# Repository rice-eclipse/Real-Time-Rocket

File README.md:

# Neutro Board
Repository stored on the raspberry pi used for Spaceport America Cup 2023 and launch test in Spring 2023. The scripts activates the sensors on Neutro, collects data, and transmit to the ground station NARWAL.

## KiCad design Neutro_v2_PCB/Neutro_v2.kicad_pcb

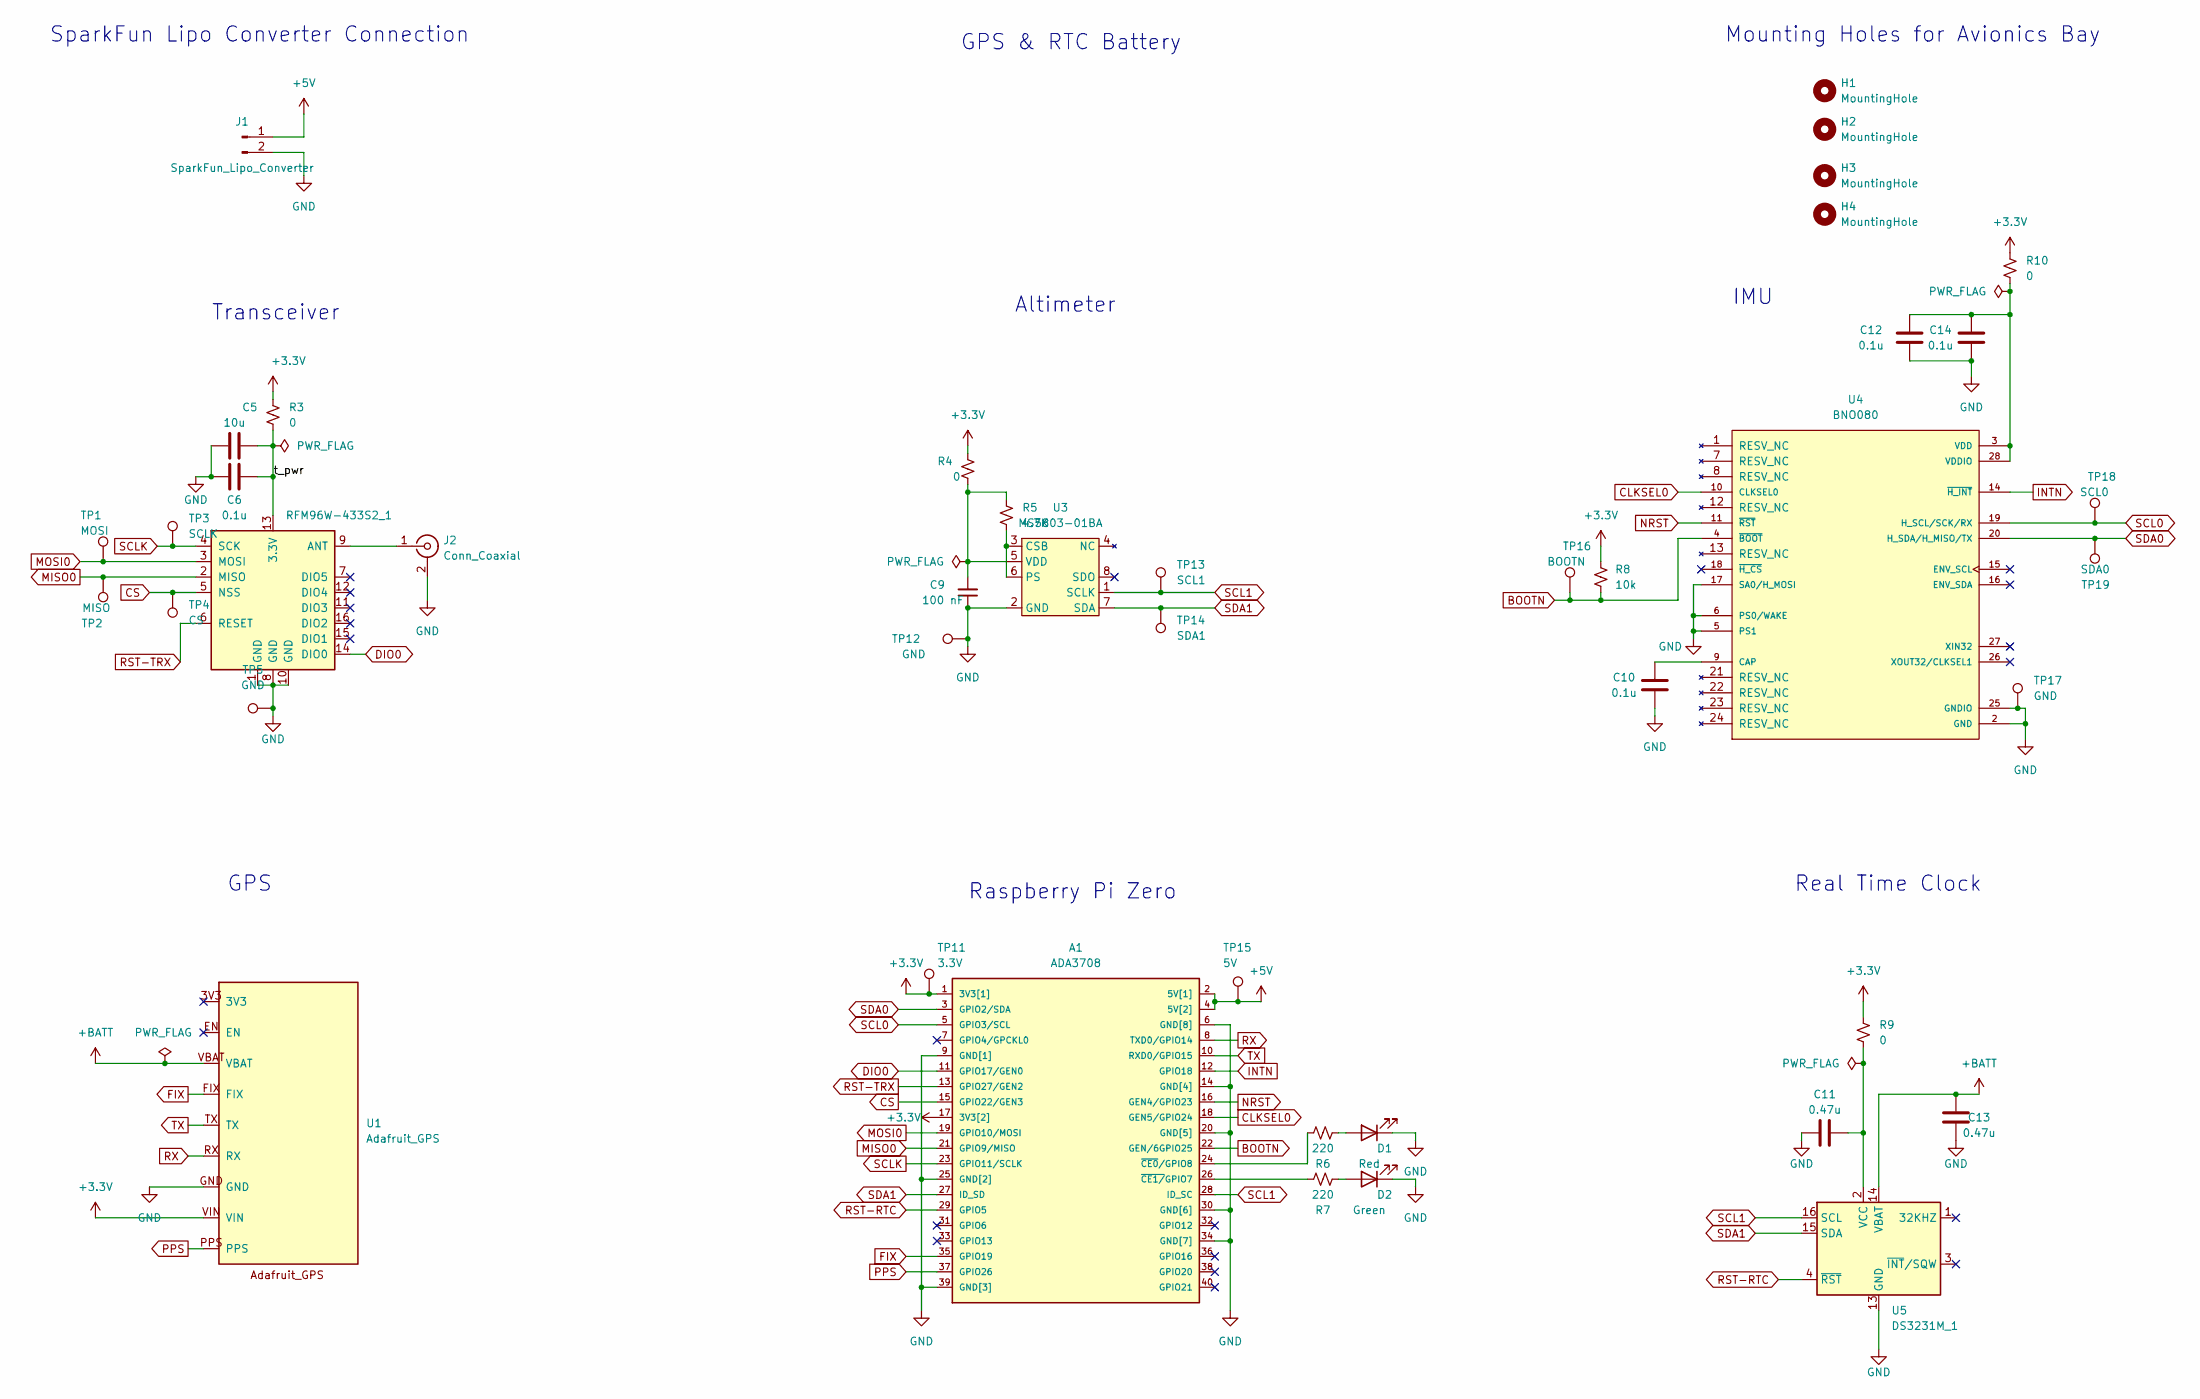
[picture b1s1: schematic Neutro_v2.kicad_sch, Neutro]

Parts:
A1: ADA3708; ADA3708_RPI-ZERO
C5: 10u; C_1206_3216Metric
C6, C10, C12, C14: 0.1u; C_1206_3216Metric
C9: 100 nF; C_1206_3216Metric
C11, C13: 0.47u; C_1206_3216Metric
D1: Red; LED_D3.0mm
D2: Green; LED_D3.0mm
H1, H2, H3, H4: MountingHole; MountingHole_2.5mm
J1: SparkFun_Lipo_Converter; Sparkfun_Lipo_Converter
J2: Conn_Coaxial; SMA_Amphenol_132203-12_Horizontal
R3, R4, R9, R10: 0; R_1206_3216Metric
R5: 4.7K; R_1206_3216Metric
R6, R7: 220; R_1206_3216Metric
R8: 10k; R_1206_3216Metric
TP1: MOSI; TestPoint_THTPad_D1.5mm_Drill0.7mm
TP2: MISO; TestPoint_THTPad_D1.5mm_Drill0.7mm
TP3: SCLK; TestPoint_THTPad_D1.5mm_Drill0.7mm
TP4: CS; TestPoint_THTPad_D1.5mm_Drill0.7mm
TP5, TP12, TP17: GND; TestPoint_THTPad_D1.5mm_Drill0.7mm
TP11: 3.3V; TestPoint_THTPad_D1.5mm_Drill0.7mm
TP13: SCL1; TestPoint_THTPad_D1.5mm_Drill0.7mm
TP14: SDA1; TestPoint_THTPad_D1.5mm_Drill0.7mm
TP15: 5V; TestPoint_THTPad_D1.5mm_Drill0.7mm
TP16: BOOTN; TestPoint_THTPad_D1.5mm_Drill0.7mm
TP18: SCL0; TestPoint_THTPad_D1.5mm_Drill0.7mm
TP19: SDA0; TestPoint_THTPad_D1.5mm_Drill0.7mm
U1: Adafruit_GPS
U2: RFM96W-433S2_1; HOPERF_RFM9XW_SMD
U3: MS5803-01BA; MS5803-01BA_Miniature_Altimeter_Module
U4: BNO080; BNO085; PARTREV 1.6
U5: DS3231M_1; DS3231M

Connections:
+3.3V: A1.1 (3V3[1]), A1.17 (3V3[2]), R3.1, R4.1, R8.1, R9.1, R10.1, TP11.1, U1.VIN
+5V: A1.2 (5V[1]), A1.4 (5V[2]), J1.1, TP15.1
+BATT: C13.1, U1.VBAT, U5.14 (VBAT)
/t_pwr: C5.2, C6.2, R3.2, U2.13 (3.3V)
BOOTN: A1.22 (GEN/6GPIO25), R8.2, TP16.1, U4.4 (~BOOT)
CLKSEL0: A1.18 (GEN5/GPIO24), U4.10 (CLKSEL0)
CS: A1.15 (GPIO22/GEN3), TP4.1, U2.5 (NSS)
DIO0: A1.11 (GPIO17/GEN0), U2.14 (DIO0)
FIX: A1.35 (GPIO19), U1.FIX
GND: A1.6 (GND[8]), A1.9 (GND[1]), A1.14 (GND[4]), A1.20 (GND[5]), A1.25 (GND[2]), A1.30 (GND[6]), A1.34 (GND[7]), A1.39 (GND[3]), C5.1, C6.1, C9.1, C10.1, C11.1, C12.1, C13.2, C14.1, D1.1 (K), D2.1 (K), J1.2, J2.2 (Ext), TP5.1, TP12.1, TP17.1, U1.GND, U2.1 (GND), U2.8 (GND), U2.10 (GND), U3.2 (GND), U4.2 (GND), U4.5 (PS1), U4.6 (PS0/WAKE), U4.17 (SA0/H_MOSI), U4.25 (GNDIO), U5.5 (GND), U5.6 (GND), U5.7 (GND), U5.8 (GND), U5.9 (GND), U5.10 (GND), U5.11 (GND), U5.12 (GND), U5.13 (GND)
INTN: A1.12 (GPIO18), U4.14 (~H_INT)
MISO0: A1.21 (GPIO9/MISO), TP2.1, U2.2 (MISO)
MOSI0: A1.19 (GPIO10/MOSI), TP1.1, U2.3 (MOSI)
NRST: A1.16 (GEN4/GPIO23), U4.11 (~RST)
unnamed: A1.24 (~CE0/GPIO8), R6.1
unnamed: A1.26 (~CE1/GPIO7), R7.1
unnamed: C9.2, R4.2, R5.1, U3.5 (VDD)
unnamed: C10.2, U4.9 (CAP)
unnamed: C11.2, R9.2, U5.2 (VCC)
unnamed: C12.2, C14.2, R10.2, U4.3 (VDD), U4.28 (VDDIO)
unnamed: D1.2 (A), R6.2
unnamed: D2.2 (A), R7.2
unnamed: J2.1 (In), U2.9 (ANT)
unnamed: R5.2, U3.3 (CSB), U3.6 (PS)
PPS: A1.37 (GPIO26), U1.PPS
RST-RTC: A1.29 (GPIO5), U5.4 (~RST)
RST-TRX: A1.13 (GPIO27/GEN2), U2.6 (RESET)
RX: A1.8 (TXD0/GPIO14), U1.RX
SCL0: A1.5 (GPIO3/SCL), TP18.1, U4.19 (H_SCL/SCK/RX)
SCL1: A1.28 (ID_SC), TP13.1, U3.1 (SCLK), U5.16 (SCL)
SCLK: A1.23 (GPIO11/SCLK), TP3.1, U2.4 (SCK)
SDA0: A1.3 (GPIO2/SDA), TP19.1, U4.20 (H_SDA/H_MISO/TX)
SDA1: A1.27 (ID_SD), TP14.1, U3.7 (SDA), U5.15 (SDA)
TX: A1.10 (RXD0/GPIO15), U1.TX

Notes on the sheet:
IMU
Raspberry Pi Zero
GPS & RTC Battery
SparkFun Lipo Converter Connection
GPS
Altimeter
Real Time Clock
Transceiver
Mounting Holes for Avionics Bay

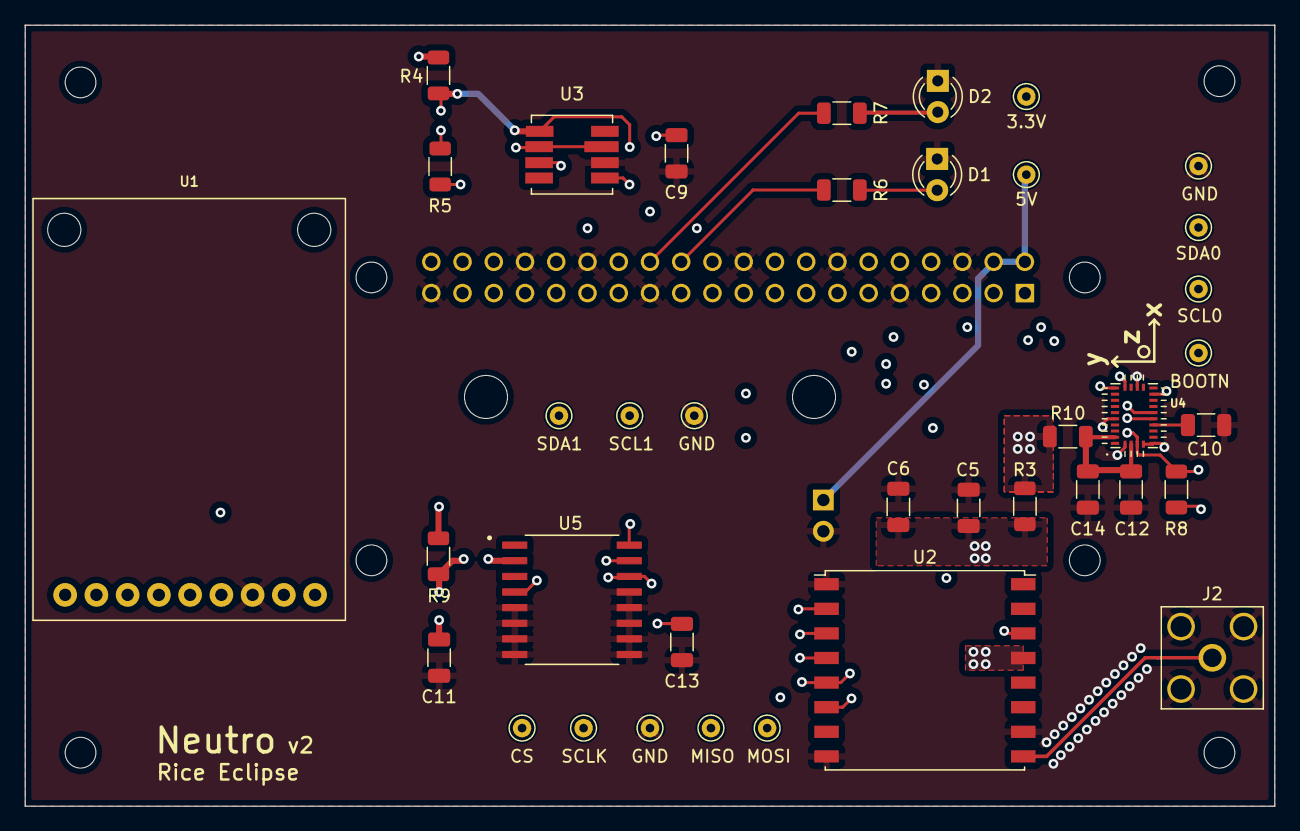
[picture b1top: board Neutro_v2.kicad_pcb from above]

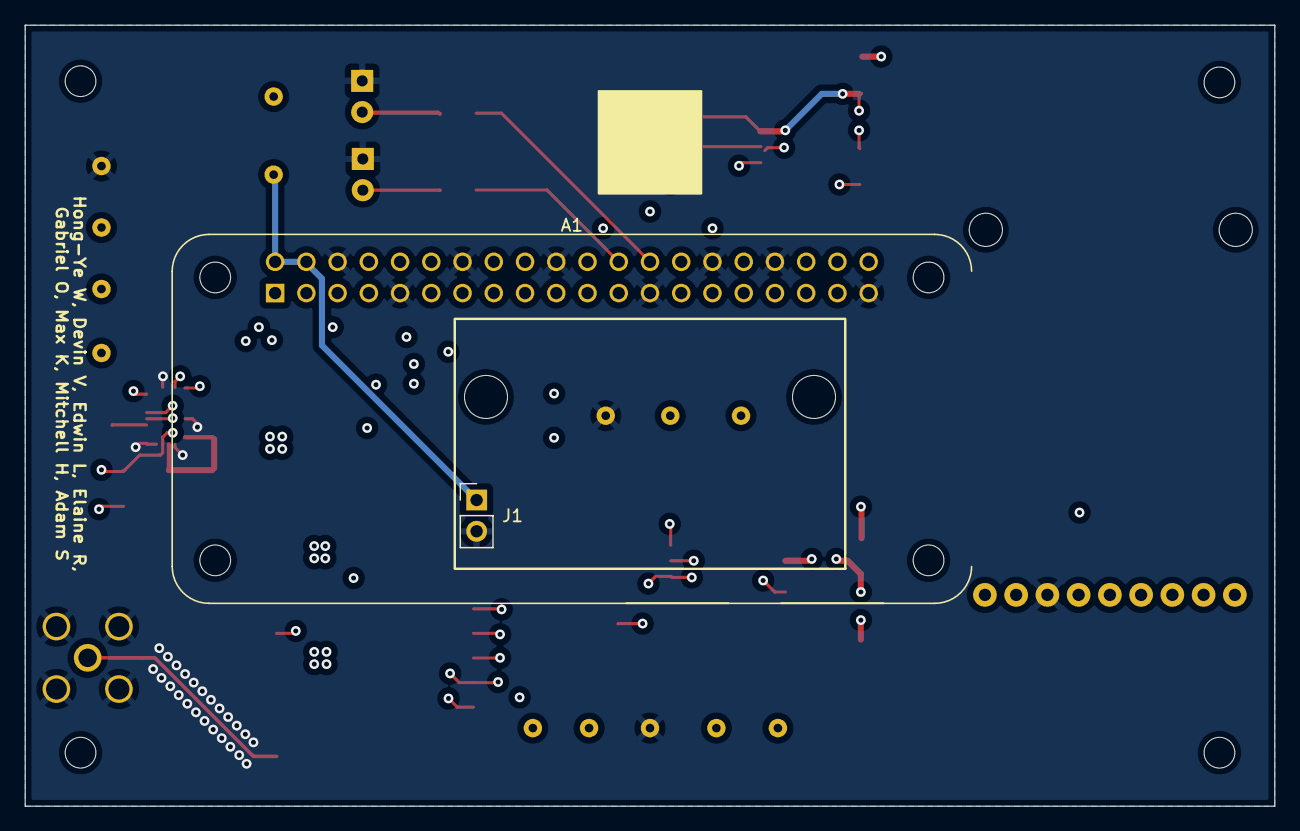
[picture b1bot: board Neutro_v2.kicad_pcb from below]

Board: 4 copper layers, 101.6 x 63.5 mm, 44 parts (2 on the bottom side), 34 nets.

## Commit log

2018-10-26 Initial commit for Real-Time-Rocket
2018-10-26 Initial Commit pt 2
2018-10-26 Rename Reciever_Code.ino to Reciever.ino
2018-10-26 Rename Transmitter_Code.ino to Transmitter.ino
2018-11-08 Added barebones transmission test for certs
    Just transmits incrementing numbers as fast as possible and logs to
    local SD. Receiver prints values to serial but does not log to any
    external source yet. Kept original factory examples in Examples folder.
2018-11-08 Added pressure/altitude/temperature sensor
2018-11-09 Created a local logging script
    Alternative to simply copy-pasting from Arduino serial monitor.
    Requires the Processing language to be installed. Put it on Hammer,
    might come in handy for the certs test.
2018-11-10 Now creates a new logfile on every run
2019-01-25 Changed Altitude function call from AltitudeFt to getAltitude
2019-01-25 Added faster transmitter code
2019-03-01 Changed pin definitions to keep consistent with Transmitter code
2019-08-13 Folder restructuring
2019-08-14 Added libraries and components for RTR
2019-08-16 Add battery holder library file
2019-08-16 Slight verification and modification of library files
2019-08-20 Add main RTR schematic (missing extra Li-Po power circuitry)
2019-08-22 Finalize schematic
2019-08-22 Add power circuitry libraries and update part footprints
2019-08-22 Add reference datasheets
2019-08-22 Update datasheets, small schematic revisions, add test pins
2019-08-24 Lay out components logically on board, miscellaneous library and schematic additions and fixes
2019-08-30 Route Board
2019-08-31 Increase size of and reroute VCC and VCC_5V traces throughout the board
2019-08-31 Update EAGLE version and small miscellaneous documentation/functionality fixes
2019-08-31 Add CAM file for ordering
2019-09-14 Added IMU datasheet
2019-09-21 Add Antenova datasheets
2019-09-21 Add symbol for M20050-1 gps
2019-09-22 initialize imu breakout project (port and imu components made)
2019-09-22 Update file names
2019-09-28 Add m20050-1 device in EAGLE
2019-09-29 added accel code
2019-10-11 Initial Commit for Transmitter code for ProtoV1
2019-10-12 Update libraries and add all sensor support
2019-10-16 Add zero calibration
2019-10-16 Clean up unnecessary files
2019-10-16 Update gitignore
2019-10-16 Add Kevin's Transciever breakout board
2019-10-16 Update names
2019-10-16 Add PCB Mill Design Rules
2019-10-19 Antenova GPS ready for mfg
2019-10-21 Add ground planes
2019-10-26 altimeter pcb files
2019-11-07 Restructure Proto folders and clean up unnecessary files
2019-11-07 Add IMU sensor library and support
2019-11-09 Add IMU Library
2019-11-09 Update packet formatting and drastic improvements to transmission rate
2019-11-09 Remove unnecessary precursor text
2019-11-14 Update packet length
2020-01-19 Add extra characters so message not cut off
2020-02-09 Reading numbers off of altimeter
2020-02-15 Improved data parsing
2020-02-23 Add remaining Sensor Breakout Boards
2020-03-05 Working pressure sensor
2020-03-05 Saved pocketbeagle files from a lost SD card
2020-03-05 git was weird
2020-10-03 Starting to rewrite code for transmitter
2020-10-03 Message byte count is only 251 :(
2020-11-07 Update Reciever.ino
    bye bye servo code
2021-02-13 Add RPI Zero W library
2021-02-13 Add sensor breakout boards
2021-02-14 Fixed a few mistakes in sensor breakouts
2021-02-14 Transceiver added to Electro II
2021-02-21 start updated gps breakout
2021-02-21 Laid out rough PCB for Electro II
2021-02-22 Lots of progress on boost converter
2021-02-22 More details on boost converter
2021-02-22 Concept trace layouts
2021-02-22 Working on ground plane concept
2021-02-23 Added sample pins and new trace ideas
2021-02-28 Created ElectroII folder
2021-02-28 Tested I2C
2021-03-06 Altimeter testing
2021-03-08 IMU_BNO085_Schematic
    Beginning work
2021-03-08 Fixed MOSI/MISO mistake
2021-03-09 Revised IMU schematic and roughed out board
2021-03-10 Laid out board + redid library for BNO
2021-03-10 Cleaned up board, see Cleanup files
2021-03-14 altimeter breakout v2
2021-03-15 Updated RPi library
2021-03-15 Board shake-ups from design review
2021-03-15 More board shuffling
2021-03-20 Reviewed traces and fixed joints
2021-03-21 some cleanup
2021-03-21 Prep for JLC?
2021-03-21 gps suffering
2021-03-22 Schematic for BNO055
2021-03-22 Updated Sketch
2021-03-26 Moved the caps to actually be useful
2021-04-04 GPS2 schematic
2021-04-04 first draft of gps breakout 2
2021-04-11 finish gpsv2
2021-04-14 actually updated the imu board, might want to check clearance before shipping it out
2021-08-27 **NEW AND IMPROVED**
    new and improved versions for a 2021 fall
2021-08-27 gps for fabrication
2021-08-27 generate cam files
2021-10-26 update gps to work with smaller inductor
2021-10-29 modified altimeter.py, new altimeter run file
2021-11-23 added data storages functionality
2021-11-23 github sucks for updating password
2021-12-04 prep for first launch
2022-02-07 update gitignore pro files
2022-02-07 fix standby and gnd gps
2022-03-27 Buck converter instead of boost
    Hopefully it works
2022-04-10 fixed with erc and drc
    should be go to go
2022-11-10 made changes to schematic, see schematic notes doc in drive
2022-11-18 update 11_17
2022-11-23 Added layout version 1 11_23_22
2022-12-02 Neutro layout revision 12.2.22
2022-12-04 neutro layout update 12.4.22
2022-12-05 layout revision 12.4.22
2022-12-24 Revision 12.24.22
2022-12-24 Neutro revision 12.24.22
2023-01-21 neutro pcb v1 final design 1.21.22
2023-01-21 neutro v1 1.21.23 final pcb (change L2, L3 size)
2023-01-22 1.22.23 final neutro v1 pcb
2023-01-23 added electroII code
2023-02-06 Added folder for neutro code
2023-02-06 added example code for BNO085
2023-02-13 add altimeter and gps code for neutro from electroII reference
2023-02-21 added led blink test
2023-02-21 add git ignore and delete DS
2023-02-21 add DS_Store to .gitignore
2023-02-21 turn off light after blinking
2023-02-21 turn led off at end of blink test
2023-02-27 verified BOM
2023-02-27 remove ds store
2023-02-27 add altimeter code
2023-02-27 transceiver code
2023-02-27 change transceiver pin
2023-02-27 modified altimeter code
2023-03-03 chat gpt altimeter code
2023-03-03 print altitude
2023-03-03 slower measure frequency
2023-03-03 added gpt gps code
2023-03-03 change to pyserial
2023-03-03 add not fix
2023-03-03 open serial test
2023-03-03 added check if gps is on
2023-03-03 add imu code
2023-03-03 add timeout
2023-03-03 check imu status
2023-03-03 check imu status remove timeout
2023-03-03 imu code no timeout
2023-03-05 turn everything on
2023-03-05 added code found online
2023-03-05 disable turn all on
2023-03-06 turn serial options on
2023-03-06 change to AMA0
2023-03-06 added print statement
2023-03-06 removed some serial arguments
2023-03-06 add line read
2023-03-06 add data
2023-03-06 change to ttys0
2023-03-19 change altimeter units
2023-03-19 delay
2023-03-19 galveston pressure
2023-03-23 added 3.25.23 testing files
2023-03-23 added stadium transmit test
2023-03-23 change config file path
2023-03-23 fix tabs
2023-03-23 remove more tabs from yaml
2023-03-23 update adafruit rfm module used
2023-03-23 update transceiver pin
2023-03-23 update altimeter packet
2023-03-23 change yaml
2023-03-23 time_ns()
2023-03-23 some chnges to struct.pack
2023-03-23 add .items()
2023-03-23 used ms5803.py module
2023-03-23 added ms5803.py
2023-03-23 change pressure unit
2023-03-23 change sea level pressure
2023-03-24 gpio26 high mode
2023-03-24 print error in except block
2023-03-24 move GPIO cleanup to the end
2023-03-24 modified code to transmit with NARWAL
2023-03-24 blink 10 times
2023-03-24 blink 50 times at boot
2023-03-24 turn off led after 5 blinks
2023-03-24 blink 100 times on boot and adjust to galveston sea pressure
2023-04-06 added neutro using adafruit gps breakout
2023-04-06 remove non pcb related files, stored in other branches
2023-04-06 test
2023-04-10 update v2 pcb
2023-04-10 update gerber file
2023-04-10 verified gps module footprint
2023-04-10 finalize gerber for jlc
2023-05-10 kicad bom file
2023-05-11 testing altimeter on neutro 2
2023-05-22 adafruit gps code example
2023-05-22 adafruit gps code example change to serial
2023-05-22 rename gps python file name
2023-05-22 remove precision format
2023-05-22 comment trx on altimeter
2023-05-22 test green LED
2023-05-22 RTR sensor final code, transmission part to be updated
2023-05-22 led check
2023-05-22 recheck led blink
2023-05-22 note on imu not working
2023-06-26 added folder for supplementary files such as JLC order setting, datasheets, and KICAD symbol footprint files
2023-08-21 Create README.md
    Added Neutro description
2023-08-21 Create README.md
    Added neutro 2 description
2023-08-21 Create README.md
    add neutro board description
